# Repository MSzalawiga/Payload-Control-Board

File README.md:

# Payload Control Board

During the 2023-2024 design cycle I was tasked with updating the Control Board for the Scientific Payload for Queen's Space Engineering Team.

I worked on 2 revisions of the board being Rev2 and Rev3 with Rev3 being the board used at competition.

These boards were created using KiCad 7.0 and were both 4 layer Signal/Ground/Power/Signal stackups.

## Revision 2
Revision 2 was done in a hurry as we needed a working control board for our systems acceptance review in late Feburary 2024, meaning I needed to order the board early December 2023 before exams started. The hurry comes from the fact that I took over this project from scratch in late November 2023.

### Scope and Functional Requirements
The scope and requirements of this control board came from the requirements from the Science and Mechanical team along with the 2024 University Rover Challenge (URC) Science mission rules. The scope and requirements were as follows:
- Control 2 Stepper Motors to raise and lower the payload
- Control up to 6 Servos for collection scoops and an auger
- Be able to toggle and change the brightness of 9 incandescent lights for the on-board spectrometer.
- Interface with the Rover through serial communication
- Interface with Sensors to get scientific measurements
### Reflection
I am content the turnout of this board, although the board was not space efficent it was able to serve its purpose in being able to provide funcionality for the systems acceptance review. 
Also since I was only able to use THT components (annoying I know) I couldn't find a buck converter with an external control pin, thankfully a weird trick I found online (can't find the articel :(  using a dac to influence the reading on the feedback pin worked wonderfully.

## Revision 3
Now having more time I created Revision 3, having mostly the same requirements with some exceptions being no more ethernet module, switch 3 lights for UV lights and the sensors switching it was pretty much the same. Also I could use SMT components (thank god). 

I am going to jump right into the reflection since the requirements were basically the same as revision 2.

### Reflection
Awesome, I am very happy with the turnout of this board. I was able to fit everything on a 100mm x 100mm board with a Teensy 4.1 microcontroller with a footprint of ~ 60mm x 25 mm. Also this was my first time soldering SMT components on a PCB so I chose 0603 (metric) to be my smallest passive size and I think it turned out well.

A new revision will be needed next year to adapt to the changing ruleset of the science mission. Next year I have taken on an executive position so I will be in more of a helper / design verification role for this specific project.

Some improvements I can think of are:
- No teensy 4.1, switch to STM32 they are just better and putting the MCU ourselves results in a smaller footprint and a more professional look
- I accidentally swapped SDA and SCL on the 3V3 I2C line (whoops) but with design verification next year this shouldn't happen
- For controlling light brightness use PWM and Transistors rather than a buck converter, the lights don't draw too much current. or use a newer buck ic with external pwm signal
- get new stepper drivers, current ones ran very hot and weren't very configurable

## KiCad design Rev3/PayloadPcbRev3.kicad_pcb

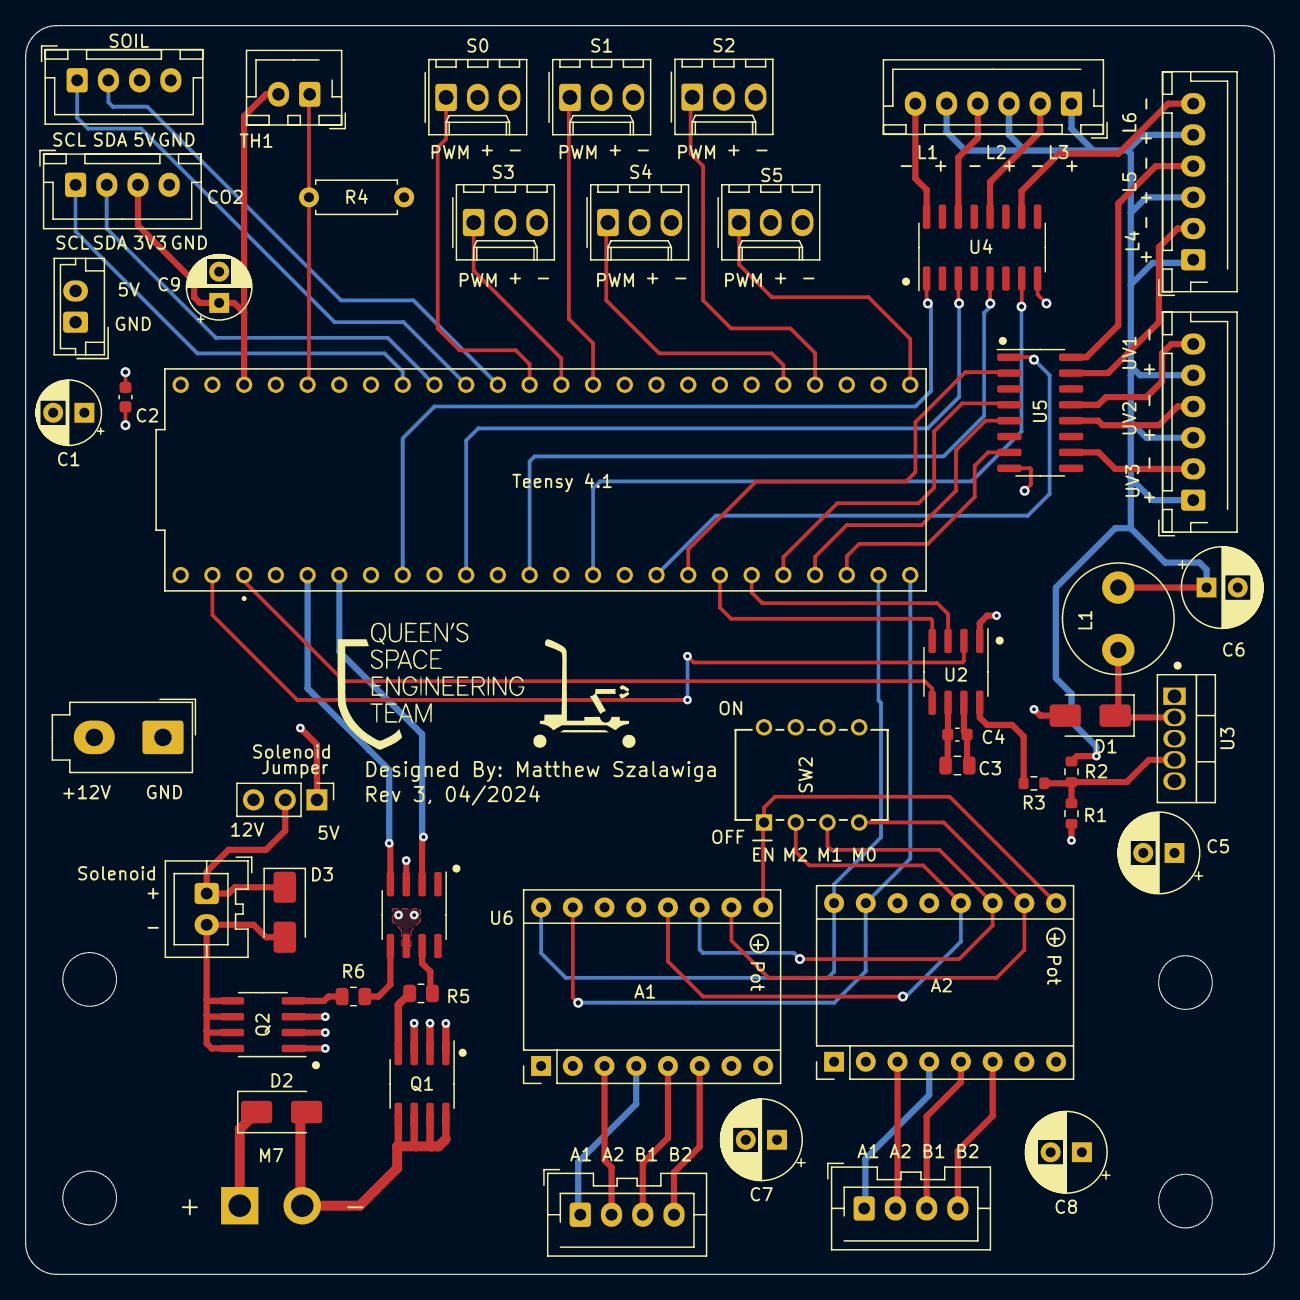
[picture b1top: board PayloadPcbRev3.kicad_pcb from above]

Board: 4 copper layers, 100.0 x 100.0 mm, 53 parts (0 on the bottom side), 64 nets.

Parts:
A1, A2: DRV8825_Stepper_Driver; Pololu_Breakout-16_15.2x20.3mm
C1, C9: 47u; CP_Radial_D5.0mm_P2.50mm
C2, C4: 100n; C_0603_1608Metric
C3: 10u; C_0805_2012Metric
C5, C6, C7, C8: 100u; CP_Radial_D6.3mm_P2.50mm
CO2: CO2 Sensor (STC31); JST_XH_B4B-XH-A_1x04_P2.50mm_Vertical
D1, D2, D3: SS54; D_SMA
H1, H2, H3, H4: MountingHole; MountingHole_4.3mm_M4
J1: Lights Row 1; JST_XH_B6B-XH-AM_1x06_P2.50mm_Vertical
J2: Lights Row 2; JST_XH_B6B-XH-AM_1x06_P2.50mm_Vertical
J3: Lights Row 3; JST_XH_B6B-XH-AM_1x06_P2.50mm_Vertical
J6: 5V Solenoid; JST_XA_B02B-XASK-1_1x02_P2.50mm_Vertical
J7: Stepper Motor 1; JST_XA_B04B-XASK-1-A_1x04_P2.50mm_Vertical
J8: Stepper Motor 2; JST_XA_B04B-XASK-1-A_1x04_P2.50mm_Vertical
J9: 12V Connector; Molex_Mini-Fit_Jr_5566-02A_2x01_P4.20mm_Vertical
J10: 5V Connector; JST_EH_B2B-EH-A_1x02_P2.50mm_Vertical
J12: Solenoid jumper; PinHeader_1x03_P2.54mm_Vertical
L1: 220u; L_Radial_D8.7mm_P5.00mm_Fastron_07HCP
M7: Motor_DC; AMASS_XT30UPB-F_1x02_P5.0mm_Vertical
Q1, Q2: AO4484; SOIC-8_3.9x4.9mm_P1.27mm
R1: 1k6; R_0603_1608Metric
R2: 10k; R_0603_1608Metric
R3: 5k1; R_0603_1608Metric
R4: 100k; R_Axial_DIN0207_L6.3mm_D2.5mm_P7.62mm_Horizontal
R5, R6: 0R; R_0805_2012Metric
S0: Servo S0; Molex_KK-254_AE-6410-03A_1x03_P2.54mm_Vertical
S1: Servo S1; Molex_KK-254_AE-6410-03A_1x03_P2.54mm_Vertical
S2: Servo S2; Molex_KK-254_AE-6410-03A_1x03_P2.54mm_Vertical
S3: Servo S3; Molex_KK-254_AE-6410-03A_1x03_P2.54mm_Vertical
S4: Servo S4; Molex_KK-254_AE-6410-03A_1x03_P2.54mm_Vertical
S5: Servo S5; Molex_KK-254_AE-6410-03A_1x03_P2.54mm_Vertical
SOIL: Adafruit STEMMA Soil Sensor; JST_XH_B4B-XH-A_1x04_P2.50mm_Vertical
SW2: SW_DIP_x04; DIP8_210-4_CTS
TH1: Thermistor; JST_XH_B2B-XH-AM_1x02_P2.50mm_Vertical
Teensy 4.1: Teensy 4.1; Teensy4-1
U2: MCP4921-ESN; SOIC-8_3.9x4.9mm_P1.27mm
U3: LM2576T-ADJ; TO-220-5_Vertical
U4, U5: ULN2003A; SOIC-16_3.9x9.9mm_P1.27mm
U6: MIC4427; SOIC-8_3.9x4.9mm_P1.27mm

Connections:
+5V: A1.13 (~RST), A1.14 (~SLP), A2.13 (~RST), A2.14 (~SLP), C1.1, C2.1, C3.1, C4.1, J10.2, J12.1, S0.2 (+), S1.2 (+), S2.2 (+), S3.2 (+), S4.2 (+), S5.2 (+), SOIL.3, SW2.5, SW2.6, SW2.7, SW2.8, Teensy 4.1.VIN, U2.1 (VDD), U2.6 (VrefA)
+12V: A1.8 (VMOT), A2.8 (VMOT), C5.1, C7.1, C8.1, D2.1 (K), J9.2, J12.3, M7.1 (+), U3.1 (VIN), U6.6 (V+)
/Lights Control/DAC_CS: Teensy 4.1.0 (GPIO0), U2.2 (~CS)
/Lights Control/DAC_MOSI: Teensy 4.1.26 (A12/GPIO26), U2.4 (SDI)
/Lights Control/DAC_SCK: Teensy 4.1.27 (A13/GPIO27), U2.3 (SCK)
/Lights Control/FB: R1.1, R2.2, R3.1, U3.4 (FB)
/Lights Control/L1: Teensy 4.1.6 (GPIO6), U4.1 (I1)
/Lights Control/L2: Teensy 4.1.8 (GPIO8), U4.3 (I3)
/Lights Control/L3: Teensy 4.1.10 (GPIO10), U4.5 (I5)
/Lights Control/L4: Teensy 4.1.12 (GPIO12), U4.7 (I7)
/Lights Control/L5: Teensy 4.1.24 (A10/GPIO24), U5.1 (I1)
/Lights Control/L6: Teensy 4.1.25 (A11/GPIO25), U5.2 (I2)
/Lights Control/LDAC: Teensy 4.1.1 (GPIO1), U2.5 (~LDAC)
/Lights Control/LM2576_Out: D1.1 (K), L1.1, U3.2 (OUT)
/Lights Control/UV1: Teensy 4.1.28 (GPIO28), U5.4 (I4)
/Lights Control/UV2: Teensy 4.1.29 (GPIO29), U5.5 (I5)
/Lights Control/UV3: Teensy 4.1.30 (GPIO30), U5.7 (I7)
/Motors/Dir: A1.16 (DIR), A2.16 (DIR), Teensy 4.1.31 (GPIO31)
/Motors/M-: D2.2 (A), M7.2 (-), Q1.5 (D), Q1.6 (D), Q1.7 (D), Q1.8 (D)
/Motors/OutA_to_R: R5.1, U6.7 (OUT_A)
/Motors/OutB_to_R: R6.1, U6.5 (OUT_B)
/Motors/Servo S0 PWM: S0.1 (PWM), Teensy 4.1.15 (A1/GPIO15)
/Motors/Servo S1 PWM: S1.1 (PWM), Teensy 4.1.13 (GPIO13)
/Motors/Servo S2 PWM: S2.1 (PWM), Teensy 4.1.36 (GPIO36)
/Motors/Servo S3 PWM: S3.1 (PWM), Teensy 4.1.14 (A0/GPIO14)
/Motors/Servo S4 PWM: S4.1 (PWM), Teensy 4.1.37 (GPIO37)
/Motors/Servo S5 PWM: S5.1 (PWM), Teensy 4.1.33 (GPIO33)
/Motors/Solenoid_+: D3.1 (K), J6.1, J12.2
/Motors/Solenoid_-: D3.2 (A), J6.2, Q2.5 (D), Q2.6 (D), Q2.7 (D), Q2.8 (D)
/Motors/Step: A1.15 (STEP), A2.15 (STEP), Teensy 4.1.32 (GPIO32)
/Motors/motor_pwm: Teensy 4.1.4 (GPIO4), U6.2 (IN_A)
/Motors/solenoid_pwm: Teensy 4.1.3 (GPIO3), U6.4 (IN_B)
/Sensors and Connectors/3V3: C9.1, CO2.3, TH1.2, Teensy 4.1.3.3V_2 (3.3V__1)
/Sensors and Connectors/I2C_SCL0: CO2.1, Teensy 4.1.19 (A5/GPIO19)
/Sensors and Connectors/I2C_SCL1: SOIL.1, Teensy 4.1.17 (A3/GPIO17)
/Sensors and Connectors/I2C_SDA0: CO2.2, Teensy 4.1.18 (A4/GPIO18)
/Sensors and Connectors/I2C_SDA1: SOIL.2, Teensy 4.1.16 (A2/GPIO16)
/Sensors and Connectors/V_Thermo: R4.1, TH1.1, Teensy 4.1.22 (A8/GPIO22)
EN_N: A1.9 (~EN), A2.9 (~EN), SW2.1
GND: A1.1 (GND), A1.7 (GND_MOT), A2.1 (GND), A2.7 (GND_MOT), C1.2, C2.2, C3.2, C4.2, C5.2, C6.2, C7.2, C8.2, C9.2, CO2.4, D1.2 (A), J9.1, J10.1, Q1.1 (S), Q1.2 (S), Q1.3 (S), Q2.1 (S), Q2.2 (S), Q2.3 (S), R1.2, R4.2, S0.3 (-), S1.3 (-), S2.3 (-), S3.3 (-), S4.3 (-), S5.3 (-), SOIL.4, Teensy 4.1.GND1 (GND), Teensy 4.1.GND2 (GND), Teensy 4.1.GND3 (GND), U2.7 (AVSS), U3.3 (GND), U3.5 (~ON/OFF), U4.8 (GND), U5.8 (GND), U6.3 (GND)
L1_GND: J1.6, U4.16 (O1)
L2_GND: J1.4, U4.14 (O3)
L3_GND: J1.2, U4.12 (O5)
L4_GND: J2.6, U4.10 (O7)
L5_GND: J2.4, U5.16 (O1)
L6_GND: J2.2, U5.15 (O2)
Light_PWR: C6.1, J1.1, J1.3, J1.5, J2.1, J2.3, J2.5, J3.1, J3.3, J3.5, L1.2, R2.1
M0: A1.10 (M0), A2.10 (M0), SW2.4
M1: A1.11 (M1), A2.11 (M1), SW2.3
M2: A1.12 (M2), A2.12 (M2), SW2.2
Step1_A1: A1.4 (A1), J7.1
Step1_A2: A1.3 (A2), J7.2
Step1_B1: A1.5 (B1), J7.3
Step1_B2: A1.6 (B2), J7.4
Step2_A1: A2.4 (A1), J8.1
Step2_A2: A2.3 (A2), J8.2
Step2_B1: A2.5 (B1), J8.3
Step2_B2: A2.6 (B2), J8.4
UV1_GND: J3.6, U5.13 (O4)
UV2_GND: J3.4, U5.12 (O5)
UV3_GND: J3.2, U5.10 (O7)
Vctrl: R3.2, U2.8 (VoutA)
motor_fet: Q1.4 (G), R5.2
solenoid_fet: Q2.4 (G), R6.2

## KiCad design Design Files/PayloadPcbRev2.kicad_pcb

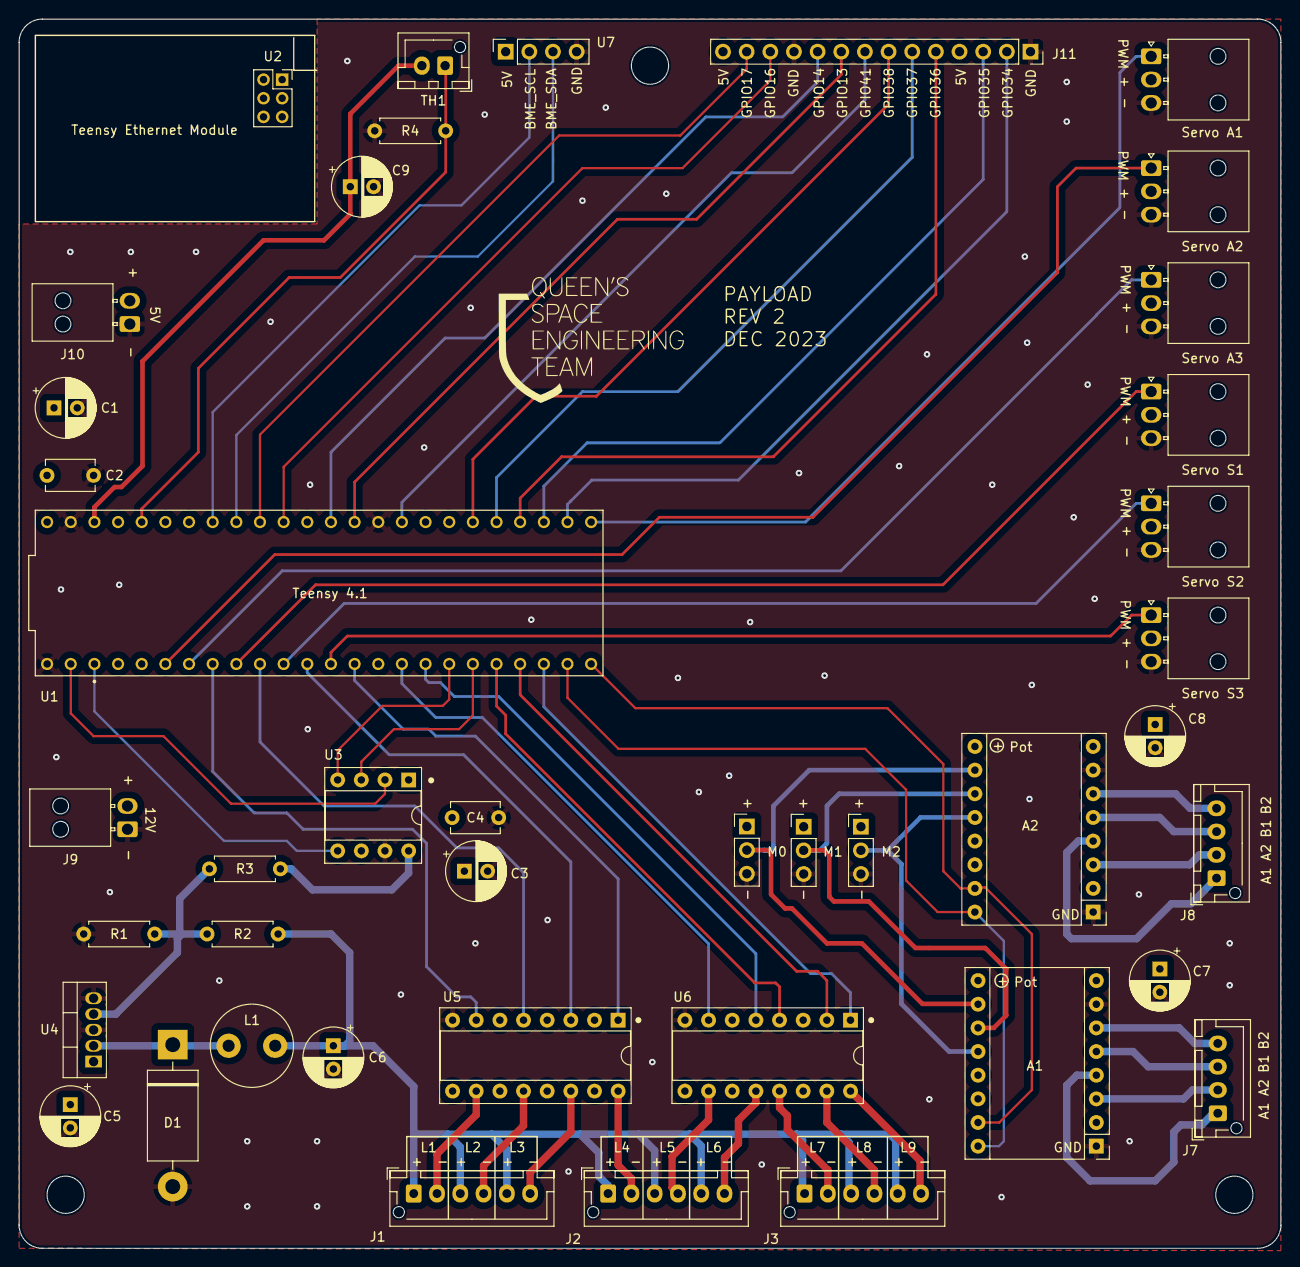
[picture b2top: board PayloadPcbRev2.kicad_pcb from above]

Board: 4 copper layers, 135.5 x 132.0 mm, 42 parts (0 on the bottom side), 62 nets.

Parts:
A1, A2: DRV8825_Stepper_Driver; Pololu_Breakout-16_15.2x20.3mm
C1, C3, C9: 47u; CP_Radial_D6.3mm_P2.50mm
C2, C4: 100n; C_Disc_D5.1mm_W3.2mm_P5.00mm
C5, C6, C7, C8: 100u; CP_Radial_D6.3mm_P2.50mm
D1: 1N5821; D_DO-201AD_P15.24mm_Horizontal
J1: Lights Row 1; JST_XH_B6B-XH-AM_1x06_P2.50mm_Vertical
J2: Lights Row 2; JST_XH_B6B-XH-AM_1x06_P2.50mm_Vertical
J3: Lights Row 3; JST_XH_B6B-XH-AM_1x06_P2.50mm_Vertical
J4: M0 Jumper; PinHeader_1x03_P2.54mm_Vertical
J5: M1 Jumper; PinHeader_1x03_P2.54mm_Vertical
J6: M2 Jumper; PinHeader_1x03_P2.54mm_Vertical
J7: Stepper Motor 1; JST_XH_B4B-XH-AM_1x04_P2.50mm_Vertical
J8: Stepper Motor 2; JST_XH_B4B-XH-AM_1x04_P2.50mm_Vertical
J9: 12V Connector; Molex_Nano-Fit_105313-xx02_1x02_P2.50mm_Horizontal
J10: 5V Connector; Molex_Nano-Fit_105313-xx02_1x02_P2.50mm_Horizontal
J11: Extra Connections Header; PinSocket_1x14_P2.54mm_Vertical
L1: 220u; L_Radial_D8.7mm_P5.00mm_Fastron_07HCP
M1: Servo A1; Molex_Nano-Fit_105313-xx03_1x03_P2.50mm_Horizontal
M2: Servo A2; Molex_Nano-Fit_105313-xx03_1x03_P2.50mm_Horizontal
M3: Servo A3; Molex_Nano-Fit_105313-xx03_1x03_P2.50mm_Horizontal
M4: Servo S1; Molex_Nano-Fit_105313-xx03_1x03_P2.50mm_Horizontal
M5: Servo S2; Molex_Nano-Fit_105313-xx03_1x03_P2.50mm_Horizontal
M6: Servo S3; Molex_Nano-Fit_105313-xx03_1x03_P2.50mm_Horizontal
R1: 1k6; R_Axial_DIN0207_L6.3mm_D2.5mm_P7.62mm_Horizontal
R2: 10k; R_Axial_DIN0207_L6.3mm_D2.5mm_P7.62mm_Horizontal
R3: 5k1; R_Axial_DIN0207_L6.3mm_D2.5mm_P7.62mm_Horizontal
R4: 100k; R_Axial_DIN0207_L6.3mm_D2.5mm_P7.62mm_Horizontal
TH1: Thermistor; JST_XH_B2B-XH-AM_1x02_P2.50mm_Vertical
U1: Teensy 4.1; Teensy4-1
U2: Teensy ETH Module Connnector; PinSocket_2x03_P2.00mm_Vertical
U3: MCP4921-EP; DIP-8_W7.62mm_Socket
U4: LM2576T-ADJG; TO-220-5_Vertical
U5, U6: ULN2003A; DIP-16_W7.62mm_Socket
U7: BME 680 Module; PinSocket_1x04_P2.54mm_Vertical

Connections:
+5V: A1.13 (~RST), A1.14 (~SLP), A2.13 (~RST), A2.14 (~SLP), C1.1, C2.1, C3.1, C4.1, J4.1, J5.1, J6.1, J10.2, J11.4, J11.14, M1.2 (+), M2.2 (+), M3.2 (+), M4.2 (+), M5.2 (+), M6.2 (+), U1.VIN, U3.1 (VDD), U3.6 (VrefA), U7.1 (Vin)
+12V: A1.8 (VMOT), A2.8 (VMOT), C5.1, C7.1, C8.1, J9.2, U4.1 (VIN)
/Lights Control/DAC_CS: U1.0 (GPIO0), U3.2 (~CS)
/Lights Control/DAC_MOSI: U1.26 (A12/GPIO26), U3.4 (SDI)
/Lights Control/DAC_SCK: U1.27 (A13/GPIO27), U3.3 (SCK)
/Lights Control/FB: R1.1, R2.2, R3.1, U4.4 (FB)
/Lights Control/L1: U1.6 (GPIO6), U5.7 (I7)
/Lights Control/L2: U1.8 (GPIO8), U5.5 (I5)
/Lights Control/L3: U1.10 (GPIO10), U5.3 (I3)
/Lights Control/L4: U1.12 (GPIO12), U5.1 (I1)
/Lights Control/L5: U1.24 (A10/GPIO24), U6.7 (I7)
/Lights Control/L6: U1.25 (A11/GPIO25), U6.5 (I5)
/Lights Control/L7: U1.28 (GPIO28), U6.4 (I4)
/Lights Control/L8: U1.29 (GPIO29), U6.2 (I2)
/Lights Control/L9: U1.30 (GPIO30), U6.1 (I1)
/Lights Control/LDAC: U1.1 (GPIO1), U3.5 (~LDAC)
/Lights Control/LM2576_Out: D1.1 (K), L1.1, U4.2 (OUT)
/Motors/Dir: A1.16 (DIR), A2.16 (DIR), U1.31 (GPIO31)
/Motors/Servo A1 PWM: M1.1 (PWM), U1.33 (GPIO33)
/Motors/Servo A2 PWM: M2.1 (PWM), U1.4 (GPIO4)
/Motors/Servo A3 PWM: M3.1 (PWM), U1.5 (GPIO5)
/Motors/Servo S1 PWM: M4.1 (PWM), U1.7 (GPIO7)
/Motors/Servo S2 PWM: M5.1 (PWM), U1.9 (GPIO9)
/Motors/Servo S3 PWM: M6.1 (PWM), U1.11 (GPIO11)
/Motors/Step: A1.15 (STEP), A2.15 (STEP), U1.32 (GPIO32)
/Sensors and Connectors/3V3: C9.1, TH1.2, U1.3.3V_2 (3.3V__1)
/Sensors and Connectors/BME_SCL: U1.19 (A5/GPIO19), U7.4 (SCK/SCL)
/Sensors and Connectors/BME_SDA: U1.18 (A4/GPIO18), U7.6 (SDI/SDA)
/Sensors and Connectors/GPIO13: J11.9, U1.13 (GPIO13)
/Sensors and Connectors/GPIO14: J11.10, U1.14 (A0/GPIO14)
/Sensors and Connectors/GPIO16: J11.12, U1.16 (A2/GPIO16)
/Sensors and Connectors/GPIO17: J11.13, U1.17 (A3/GPIO17)
/Sensors and Connectors/GPIO34: J11.2, U1.34 (GPIO34)
/Sensors and Connectors/GPIO35: J11.3, U1.35 (GPIO35)
/Sensors and Connectors/GPIO36: J11.5, U1.36 (GPIO36)
/Sensors and Connectors/GPIO37: J11.6, U1.37 (GPIO37)
/Sensors and Connectors/GPIO38: J11.7, U1.38 (A14/GPIO38)
/Sensors and Connectors/GPIO41: J11.8, U1.41 (A17/GPIO41)
/Sensors and Connectors/V_Thermo: R4.1, TH1.1, U1.22 (A8/GPIO22)
GND: A1.1 (GND), A1.7 (GND_MOT), A2.1 (GND), A2.7 (GND_MOT), C1.2, C2.2, C3.2, C4.2, C5.2, C6.2, C7.2, C8.2, C9.2, D1.2 (A), J4.3, J5.3, J6.3, J9.1, J10.1, J11.1, J11.11, M1.3 (-), M2.3 (-), M3.3 (-), M4.3 (-), M5.3 (-), M6.3 (-), R1.2, R4.2, U1.GND1 (GND), U1.GND2 (GND), U1.GND3 (GND), U3.7 (AVSS), U4.3 (GND), U4.5 (~ON/OFF), U5.8 (GND), U6.8 (GND), U7.3 (GND)
L1_GND: J1.2, U5.10 (O7)
L2_GND: J1.4, U5.12 (O5)
L3_GND: J1.6, U5.14 (O3)
L4_GND: J2.2, U5.16 (O1)
L5_GND: J2.4, U6.10 (O7)
L6_GND: J2.6, U6.12 (O5)
L7_GND: J3.2, U6.13 (O4)
L8_GND: J3.4, U6.15 (O2)
L9_GND: J3.6, U6.16 (O1)
Light_PWR: C6.1, J1.1, J1.3, J1.5, J2.1, J2.3, J2.5, J3.1, J3.3, J3.5, L1.2, R2.1
M0: A1.10 (M0), A2.10 (M0), J4.2
M1: A1.11 (M1), A2.11 (M1), J5.2
M2: A1.12 (M2), A2.12 (M2), J6.2
Step1_A1: A1.4 (A1), J7.1
Step1_A2: A1.3 (A2), J7.2
Step1_B1: A1.5 (B1), J7.3
Step1_B2: A1.6 (B2), J7.4
Step2_A1: A2.4 (A1), J8.1
Step2_A2: A2.3 (A2), J8.2
Step2_B1: A2.5 (B1), J8.3
Step2_B2: A2.6 (B2), J8.4
Vctrl: R3.2, U3.8 (VoutA)

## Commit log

2024-01-13 Uploaded Design Files
2024-06-18 added Rev3
2024-06-18 Update README.md
    adding descriptions of each revision
